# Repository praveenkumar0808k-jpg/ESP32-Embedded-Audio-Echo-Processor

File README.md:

# ESP32-Embedded-Audio-Echo-Processor

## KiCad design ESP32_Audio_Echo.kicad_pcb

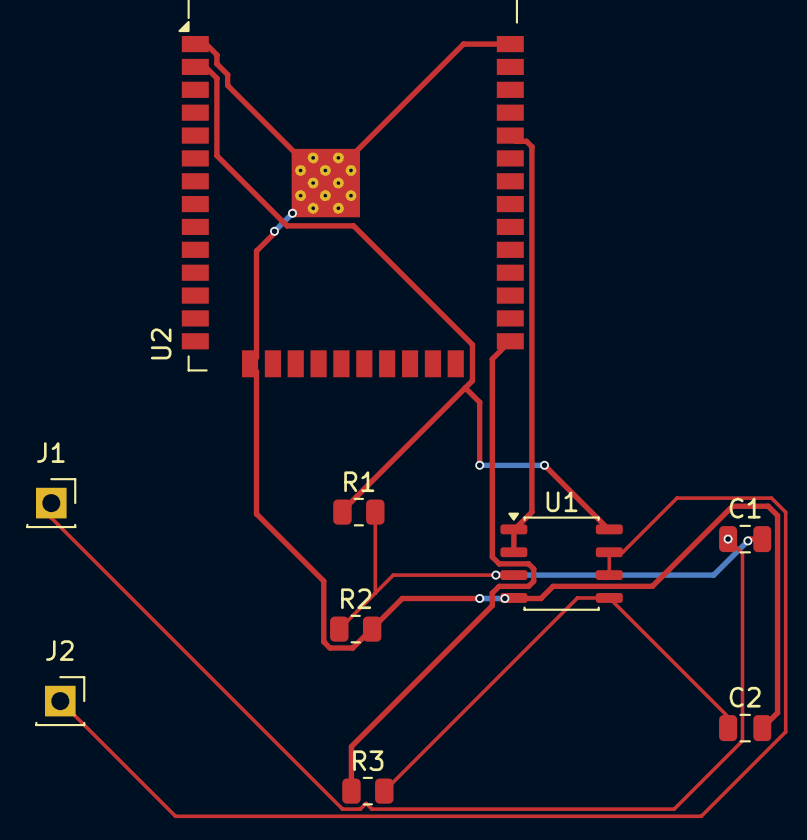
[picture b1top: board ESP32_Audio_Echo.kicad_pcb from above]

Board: 2 copper layers, 9 parts (0 on the bottom side), 8 nets.

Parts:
C1: 10u; C_0805_2012Metric
C2: 10n; C_0805_2012Metric
J1, J2: Conn_01x01_Pin; PinSocket_1x01_P2.54mm_Vertical
R1, R2: 10k; R_0805_2012Metric
R3: 1k; R_0805_2012Metric
U1: TL072; JEITA_SOIC-8_3.9x4.9mm_P1.27mm
U2: ESP32-WROOM-32D

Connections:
+3V3: R1.1, U1.8 (V+), U2.2 (VDD)
/AUDIO_TO_ESP32: U1.1, U1.2 (-), U2.34 (RXD0/IO3)
GND: C2.2, R2.2, U1.4 (V-), U2.1 (GND), U2.15 (GND), U2.38 (GND), U2.39 (GND)
unnamed: C1.1, J1.1 (Pin_1_1)
unnamed: J2.1 (Pin_1_1), U1.6 (-), U1.7
unnamed: C1.2, R1.2, R2.1, U1.3 (+)
unnamed: C2.1, R3.2, U1.5 (+)
unnamed: R3.1, U2.25 (IO0)
